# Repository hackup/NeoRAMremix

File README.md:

# NeoRAM Remix

The NeoRAM is a RAM extension for the Commodore 64/128 computers that is compatible with the GeoRAM modules. It features up to 2MB of RAM and it is battery buffered. A single CR2032 cell will usually preserve the data stored in the NeoRAM for several months.

The "remix" version is based on the [original NeoRAM](http://www.x1541.de/) developed by Nicolas Welte in 2006. Without further consent, both the original and the remix version are licensed for personal and non-commercial use only (see details below). There is also no warranty whatsoever. **USE AT YOUR OWN RISK!**.

## Configurations

The NeoRAM can be assembled in different configurations. By default, the PCB is configured for 2MB of RAM and battery buffering. There is no need to change any of the solder jumpers if the board is assembled completely.

If you choose to fit fewer RAM chips their respective decoupling caps can be omitted as well. The solder jumpers SJ3 and SJ4 on the backside of the PCB have to be changed to reflect the memory configuration:

| RAM    | SJ3 | SJ4 | ICs   | Caps  |
|--------|-----|-----|-------|-------|
| 2MB    | 1-2 | 1-2 | U1-U4 | C2-C5 |
| 1MB    | 1-2 | 2-3 | U1-U2 | C2-C3 |
| 512kB  | 2-3 | 2-3 | U1    | C2    |

If you decide you don't need the battery buffering, the following components can be omitted: BT1, D1, C1, R1-3, Q1. If you skip these components you need to close the solder jumper SJ5 on the back of the PCB. Also note that D2 is still required.

See the [NeoRAM Remix blog post](https://www.hackup.net/2019/04/the-neoram-remix/) for more details and the bill of materials.

## License
[
](http://creativecommons.org/licenses/by-nc-sa/4.0/)

This work is licensed under a
[Creative Commons Attribution-NonCommercial-ShareAlike 4.0 International License](http://creativecommons.org/licenses/by-nc-sa/4.0/).

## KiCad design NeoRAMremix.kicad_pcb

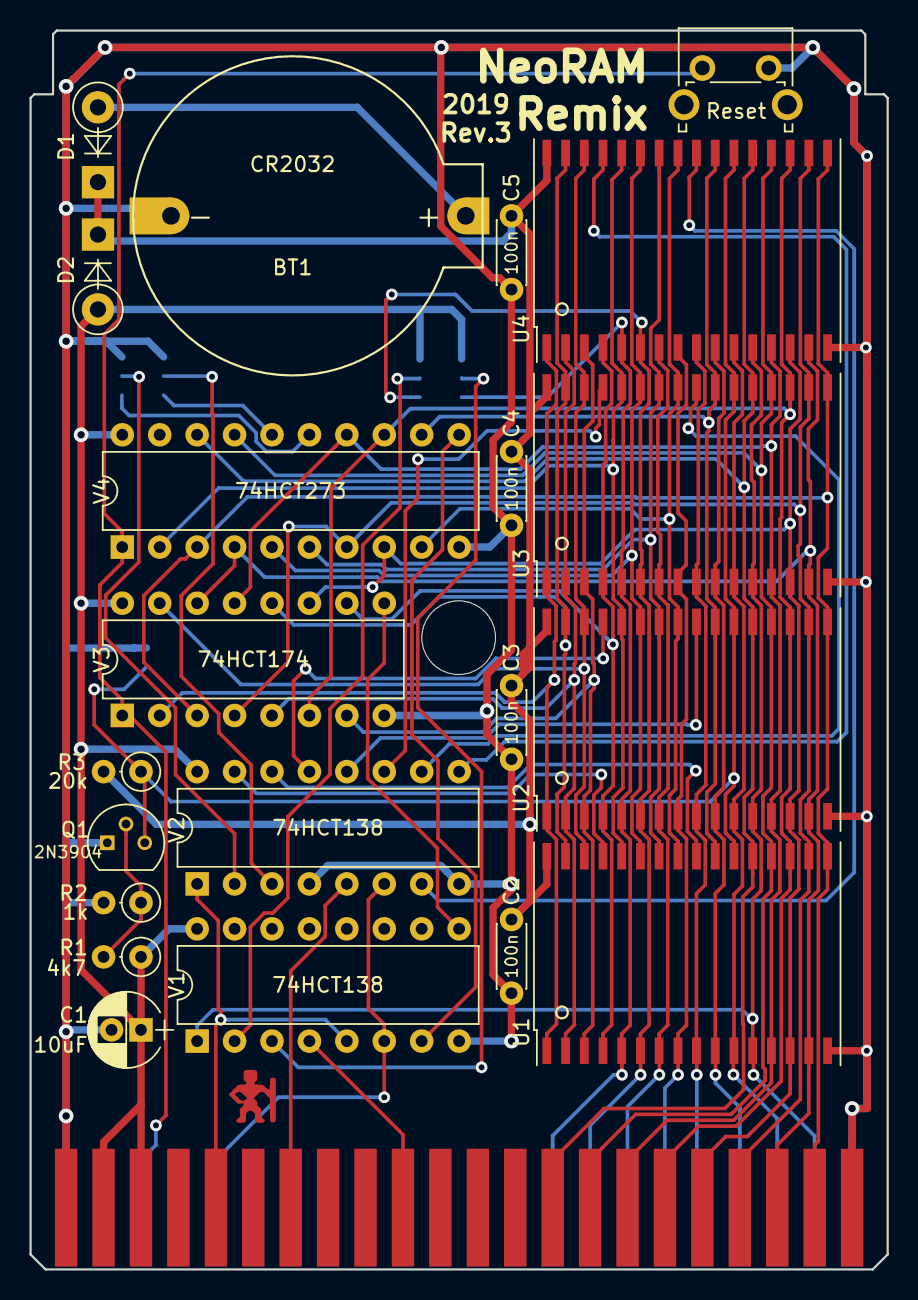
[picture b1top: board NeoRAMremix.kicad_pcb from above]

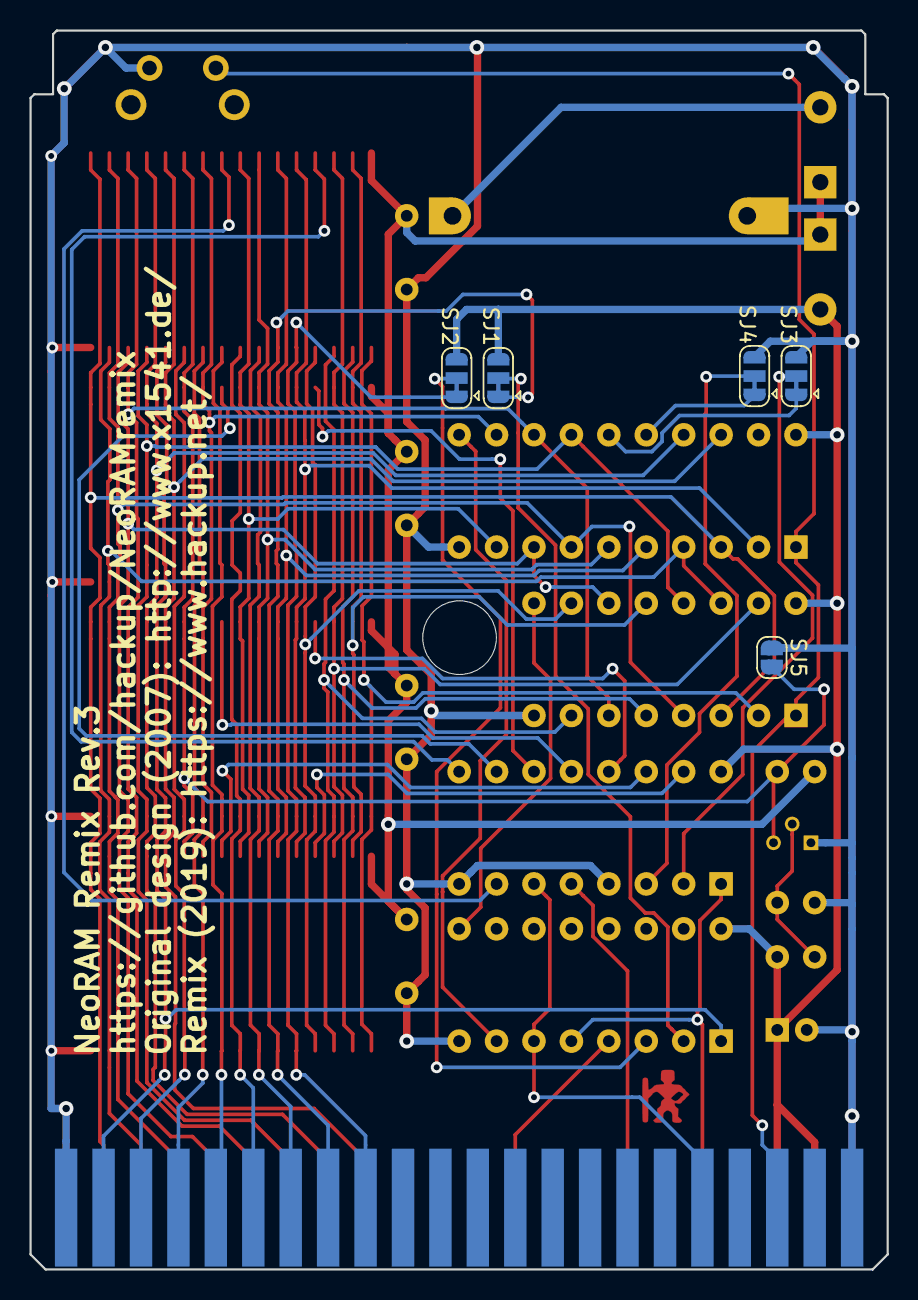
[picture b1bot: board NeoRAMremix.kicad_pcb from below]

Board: 2 copper layers, 58.2 x 84.1 mm, 28 parts (5 on the bottom side), 54 nets.

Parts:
BT1: CR2032; Battery-Holder-CR2032
C1: 10uF; CP_Radial_D5.0mm_P2.00mm
C2, C3, C4, C5: 100n; C_Disc_D4.3mm_W1.9mm_P5.00mm
D1, D2: 1N5817; D_DO-41_SOD81_P5.08mm_Vertical_KathodeUp
H1: MountingHole; MountingHole_5mm
P1: C64-Exp-Port; C64-Cart-NoSilkS
Q1: 2N3904; TO-92_Molded_Narrow
R1: 4k7; R_Axial_DIN0207_L6.3mm_D2.5mm_P2.54mm_Vertical
R2: 1k; R_Axial_DIN0207_L6.3mm_D2.5mm_P2.54mm_Vertical
R3: 20k; R_Axial_DIN0207_L6.3mm_D2.5mm_P2.54mm_Vertical
SJ1, SJ2, SJ3, SJ4: SolderJumper_3_Bridged12; SolderJumper-3_P1.3mm_Bridged12
SJ5: no_battery; SolderJumper-2_P1.3mm_Open_RoundedPad1.0x1.5mm
SW1: Reset; SW_Tactile_SPST_Angled_PTS645Vx83-2LFS
U1, U2, U3, U4: HM628512BFP-5; SO32_FP32D_20.45x11.3mm_Pitch1.27mm
V1, V2: 74HCT138; DIP-16_W7.62mm
V3: 74HCT174; DIP-16_W7.62mm
V4: 74HCT273; DIP-20_W7.62mm

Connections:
+5V: C1.1, D2.2, P1.2, P1.3, R1.1, SJ1.3, SJ2.3, V1.16, V2.16, V3.16, V4.20
+BATT: C2.1, C3.1, C4.1, C5.1, D1.1, D2.1, R3.2, U1.32, U2.32, U3.32, U4.32
/A0: P1.Y, U1.12, U2.12, U3.12, U4.12, V1.1
/A1: P1.X, U1.11, U2.11, U3.11, U4.11
/A2: P1.W, U1.10, U2.10, U3.10, U4.10
/A3: P1.V, U1.9, U2.9, U3.9, U4.9
/A4: P1.U, U1.8, U2.8, U3.8, U4.8
/A5: P1.T, U1.7, U2.7, U3.7, U4.7
/A6: P1.S, SJ1.1, U1.6, U2.6, U3.6, U4.6
/A7: P1.R, SJ2.1, U1.5, U2.5, U3.5, U4.5
/D0: P1.16, U1.13, U2.13, U3.13, U4.13, V3.13, V4.14
/D1: P1.18, U1.14, U2.14, U3.14, U4.14, V3.11, V4.8
/D2: P1.20, U1.15, U2.15, U3.15, U4.15, V3.14, V4.4
/D3: P1.21, U1.17, U2.17, U3.17, U4.17, V3.3, V4.3
/D4: P1.19, U1.18, U2.18, U3.18, U4.18, V3.4, V4.7
/D5: P1.17, U1.19, U2.19, U3.19, U4.19, V3.6, V4.13
/D6: P1.15, U1.20, U2.20, U3.20, U4.20, V4.17
/D7: P1.14, U1.21, U2.21, U3.21, U4.21, V4.18
/RA8: U1.27, U2.27, U3.27, U4.27, V4.5
/RA9: U1.26, U2.26, U3.26, U4.26, V4.6
/RA10: U1.23, U2.23, U3.23, U4.23, V4.12
/RA11: U1.25, U2.25, U3.25, U4.25, V4.9
/RA12: U1.4, U2.4, U3.4, U4.4, V3.10
/RA13: U1.28, U2.28, U3.28, U4.28, V4.2
/RA14: U1.3, U2.3, U3.3, U4.3, V3.7
/RA15: U1.31, U2.31, U3.31, U4.31, V3.12
/RA16: U1.2, U2.2, U3.2, U4.2, V3.5
/RA17: U1.30, U2.30, U3.30, U4.30, V3.15
/RA18: U1.1, U2.1, U3.1, U4.1, V3.2
GND: BT1.2, C1.2, C2.2, C3.2, C4.2, C5.2, P1.1, P1.22, P1.A, P1.Z, Q1.1, R2.2, SJ3.3, SJ4.3, SJ5.1, SW1.2, U1.16, U2.16, U3.16, U4.16, V1.8, V2.4, V2.8, V3.8, V4.10
unnamed: BT1.1, D1.2
unnamed: P1.5, V1.5, V2.1
unnamed: P1.7, V2.5
unnamed: P1.10, V1.4
unnamed: P1.C, SW1.1, V3.1, V4.1
unnamed: P1.E, V1.6, V2.6
unnamed: Q1.2, R1.2, R2.1
unnamed: Q1.3, R3.1, SJ5.2, U1.22, U2.22, U3.22, U4.22
unnamed: SJ1.2, V1.2
unnamed: SJ2.2, V1.3
unnamed: SJ3.1, V4.15
unnamed: SJ3.2, V2.2
unnamed: SJ4.1, V4.16
unnamed: SJ4.2, V2.3
unnamed: U1.24, V2.14
unnamed: U1.29, V2.15
unnamed: U2.24, V2.12
unnamed: U2.29, V2.13
unnamed: U3.24, V2.10
unnamed: U3.29, V2.11
unnamed: U4.24, V2.7
unnamed: U4.29, V2.9
unnamed: V1.7, V4.11
unnamed: V1.9, V3.9

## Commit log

2019-01-08 Initial import.
2019-01-09 Completed and fixed schematics.
2019-01-10 Started layout.
2019-01-10 More layout.
2019-01-10 First complete layout.
2019-01-10 Reset switch.
2019-01-11 Fixed solder bridges.
2019-01-11 Reduced board size and updated layout.
2019-01-14 Reduced board width.
2019-01-16 Fixing RAM footprint.
2019-01-17 Preparing for rev.1
2019-04-19 Fixed footprint.
2019-04-28 Added license info.
2019-04-28 Added JP1 to disable battery circuit for /CS.
2019-04-28 Added repo URL.
2019-04-28 More room for JP1.
2019-04-28 Improved solder jumper footprint.
2019-05-01 Replaced JP1 with solder jumber SJ5.
2019-05-01 Added preview images.
2019-05-02 Fixed Makefile.
2019-05-08 Updated battery holder again.
2019-05-25 Added photos.
2019-05-25 Added readme.
2019-05-25 Fixed file names.
2019-05-25 Added Gerber files to repo.
2020-03-08 Fixed revision number on bottom side.
